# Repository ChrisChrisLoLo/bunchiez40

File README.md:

# bunchiez40
An experimental ultraportable keyboard that uses mouse switches to achieve a compact form factor while still being viable as a daily use keyboard. Board can be hand soldered, and case can be 3D printed or CNC'd.

Has science gone too far?

# Status
v0.0 PCBs confirmed to be working! Happy to open up this project for others to play with

# About
I hit the limit as how small I could go with choc switches. I found that kailh mute switches are an ideal small form factor alternative in terms of their size, durability, and actuation force. To make this board more accessible to build at home, it uses a rp2040-zero board that can be soldered on.

More details about my research on mouse switches and experience with the bunchiez40 can be found here: https://chrischrislolo.github.io/orthoLabLogs/bunchiez40-how-i-built-a-keyboard-using-mouse-switches.html

Case files include STLs, STEP files, as well as source OpenSCAD files that can be modified. The OpenSCAD models do not have fillets on them

# Case
The case files can be found in the `case` directory. The particular files you'll want are the `case_holes` file for the top part of the case, and the `case_holes_floor` file for the bottom part. CNC and 3DP works with the top part of the case, and I chose to 3DP my case bottom.

## PCB
You can find the PCB source files in the `pcb` folder. The BOM files can be found in this folder.

## Directory Structure
- `case`
    You can find the files you need in this folder to print out a case for the keyboard
- `drafts`
    Stores any KLE or intermediate information used in making the case
- `outlines`
    Outlines used to create the case and pcb
- `pcb`
    Kicad project relating to the project
   
## BOM
- 1 PCB
- 1 Aluminum CNC upper case or 3DP upper case
- 1 lower case. I 3D printed mine
- 16 3mm M1.6 screws (go for flathead for a flush fit, though other head types should also work)
- 4-8 (ideally 8) 1-2mm bumpons (something like Sj5302 is a good place to start)
- 1 0.91 inch OLED
- 1 rp2040-zero pcb
- 40 Kailh/Huano 7.3mm mute switches (ideally with some spares)
- 40 LL4148 diodes (ideally with some spares)

## Assembly
Build guide coming soon. For now, hopefully the footprints make it clear as to what should go where. Note that the rp2040-zero should be placed in such a way that the MCU is on "top" of the pcb when the assembly is face up, like such.

Once all parts have been assembled, the board can be screwed onto the top of the case with 8 screws.

The firmware should then be flashed onto the board.

The bottom of the board can then be screwed to the case. My recommendation is to put two bumpons on each corner of the bottom of the case, one above the screw and one beside the screw. This helps maximize stability.  

## Firmware
QMK Firmware can be found here
https://github.com/ChrisChrisLoLo/vial-qmk/tree/sporewoh/keyboards/sporewoh/bunchiez40

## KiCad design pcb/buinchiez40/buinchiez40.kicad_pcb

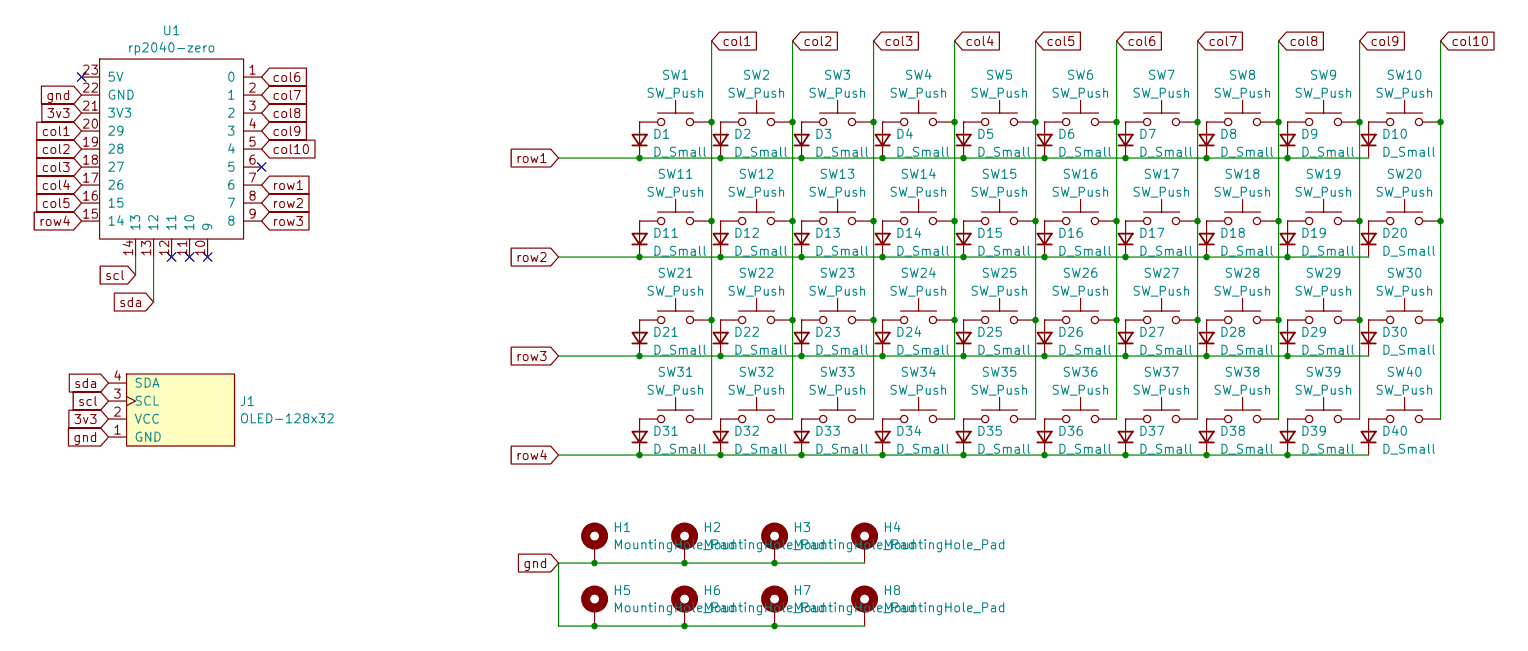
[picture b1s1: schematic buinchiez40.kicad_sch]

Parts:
D1, D2, D3, D4, D5, D6, D7, D8, D9, D10, D11, D12, D13, D14, D15, D16, D17, D18, D19, D20, D21, D22, D23, D24, D25, D26, D27, D28, D29, D30, D31, D32, D33, D34, D35, D36, D37, D38, D39, D40: D_Small; D_MiniMELF
H1, H2, H3, H4, H5, H6, H7, H8: MountingHole_Pad; m1.6_hole
J1: OLED-128x32; OLED-128x32-cutout
SW1, SW2, SW3, SW4, SW5, SW6, SW7, SW8, SW9, SW10, SW11, SW12, SW13, SW14, SW15, SW16, SW17, SW18, SW19, SW20, SW21, SW22, SW23, SW24, SW25, SW26, SW27, SW28, SW29, SW30, SW31, SW32, SW33, SW34, SW35, SW36, SW37, SW38, SW39, SW40: SW_Push; Button_Mute_Kailh
U1: rp2040-zero; rp2040-zero-tht

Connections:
3v3: J1.2 (VCC), U1.21 (3V3)
unnamed: D1.2 (A), SW1.1
unnamed: D2.2 (A), SW2.1
unnamed: D3.2 (A), SW3.1
unnamed: D4.2 (A), SW4.1
unnamed: D5.2 (A), SW5.1
unnamed: D6.2 (A), SW6.1
unnamed: D7.2 (A), SW7.1
unnamed: D8.2 (A), SW8.1
unnamed: D9.2 (A), SW9.1
unnamed: D10.2 (A), SW10.1
unnamed: D11.2 (A), SW11.1
unnamed: D12.2 (A), SW12.1
unnamed: D13.2 (A), SW13.1
unnamed: D14.2 (A), SW14.1
unnamed: D15.2 (A), SW15.1
unnamed: D16.2 (A), SW16.1
unnamed: D17.2 (A), SW17.1
unnamed: D18.2 (A), SW18.1
unnamed: D19.2 (A), SW19.1
unnamed: D20.2 (A), SW20.1
unnamed: D21.2 (A), SW21.1
unnamed: D22.2 (A), SW22.1
unnamed: D23.2 (A), SW23.1
unnamed: D24.2 (A), SW24.1
unnamed: D25.2 (A), SW25.1
unnamed: D26.2 (A), SW26.1
unnamed: D27.2 (A), SW27.1
unnamed: D28.2 (A), SW28.1
unnamed: D29.2 (A), SW29.1
unnamed: D30.2 (A), SW30.1
unnamed: D31.2 (A), SW31.1
unnamed: D32.2 (A), SW32.1
unnamed: D33.2 (A), SW33.1
unnamed: D34.2 (A), SW34.1
unnamed: D35.2 (A), SW35.1
unnamed: D36.2 (A), SW36.1
unnamed: D37.2 (A), SW37.1
unnamed: D38.2 (A), SW38.1
unnamed: D39.2 (A), SW39.1
unnamed: D40.2 (A), SW40.1
col1: SW1.2, SW11.2, SW21.2, SW31.2, U1.20 (29)
col2: SW2.2, SW12.2, SW22.2, SW32.2, U1.19 (28)
col3: SW3.2, SW13.2, SW23.2, SW33.2, U1.18 (27)
col4: SW4.2, SW14.2, SW24.2, SW34.2, U1.17 (26)
col5: SW5.2, SW15.2, SW25.2, SW35.2, U1.16 (15)
col6: SW6.2, SW16.2, SW26.2, SW36.2, U1.1 (0)
col7: SW7.2, SW17.2, SW27.2, SW37.2, U1.2 (1)
col8: SW8.2, SW18.2, SW28.2, SW38.2, U1.3 (2)
col9: SW9.2, SW19.2, SW29.2, SW39.2, U1.4 (3)
col10: SW10.2, SW20.2, SW30.2, SW40.2, U1.5 (4)
gnd: H1.1, H2.1, H3.1, H4.1, H5.1, H6.1, H7.1, H8.1, J1.1 (GND), U1.22 (GND)
row1: D1.1 (K), D2.1 (K), D3.1 (K), D4.1 (K), D5.1 (K), D6.1 (K), D7.1 (K), D8.1 (K), D9.1 (K), D10.1 (K), U1.7 (6)
row2: D11.1 (K), D12.1 (K), D13.1 (K), D14.1 (K), D15.1 (K), D16.1 (K), D17.1 (K), D18.1 (K), D19.1 (K), D20.1 (K), U1.8 (7)
row3: D21.1 (K), D22.1 (K), D23.1 (K), D24.1 (K), D25.1 (K), D26.1 (K), D27.1 (K), D28.1 (K), D29.1 (K), D30.1 (K), U1.9 (8)
row4: D31.1 (K), D32.1 (K), D33.1 (K), D34.1 (K), D35.1 (K), D36.1 (K), D37.1 (K), D38.1 (K), D39.1 (K), D40.1 (K), U1.15 (14)
scl: J1.3 (SCL), U1.14 (13)
sda: J1.4 (SDA), U1.13 (12)

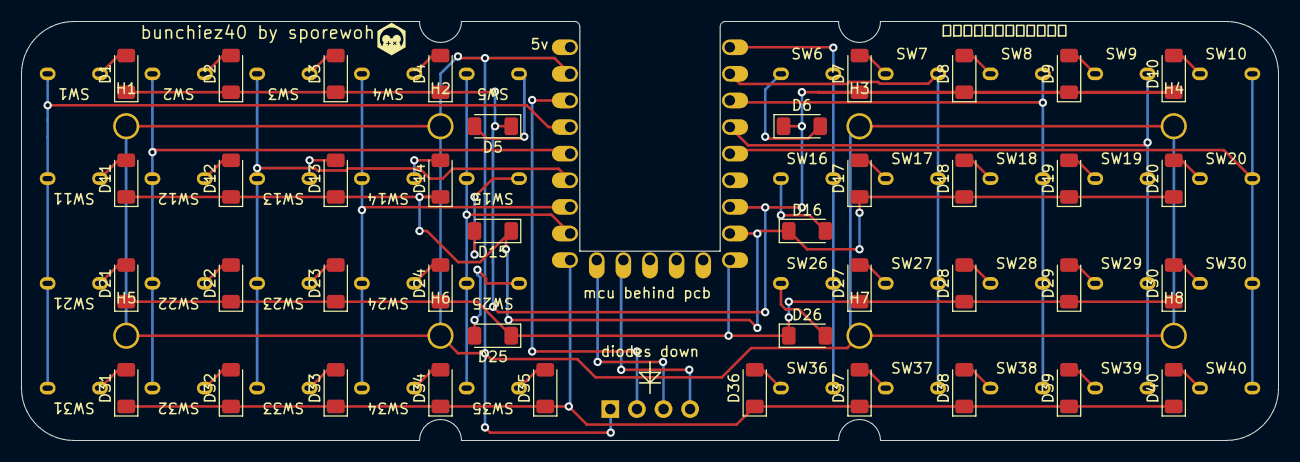
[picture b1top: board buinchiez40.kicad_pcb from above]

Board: 2 copper layers, 120.0 x 40.0 mm, 90 parts (1 on the bottom side), 58 nets.

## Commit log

2023-10-13 add case
2023-10-14 add case iterations
2023-10-14 add membrane
2023-10-15 add and export pcb
2023-11-05 add pcb output and cases
2023-11-25 add grounding pads
2023-11-28 add drawings and photos
2023-11-28 reorganize CAD files
